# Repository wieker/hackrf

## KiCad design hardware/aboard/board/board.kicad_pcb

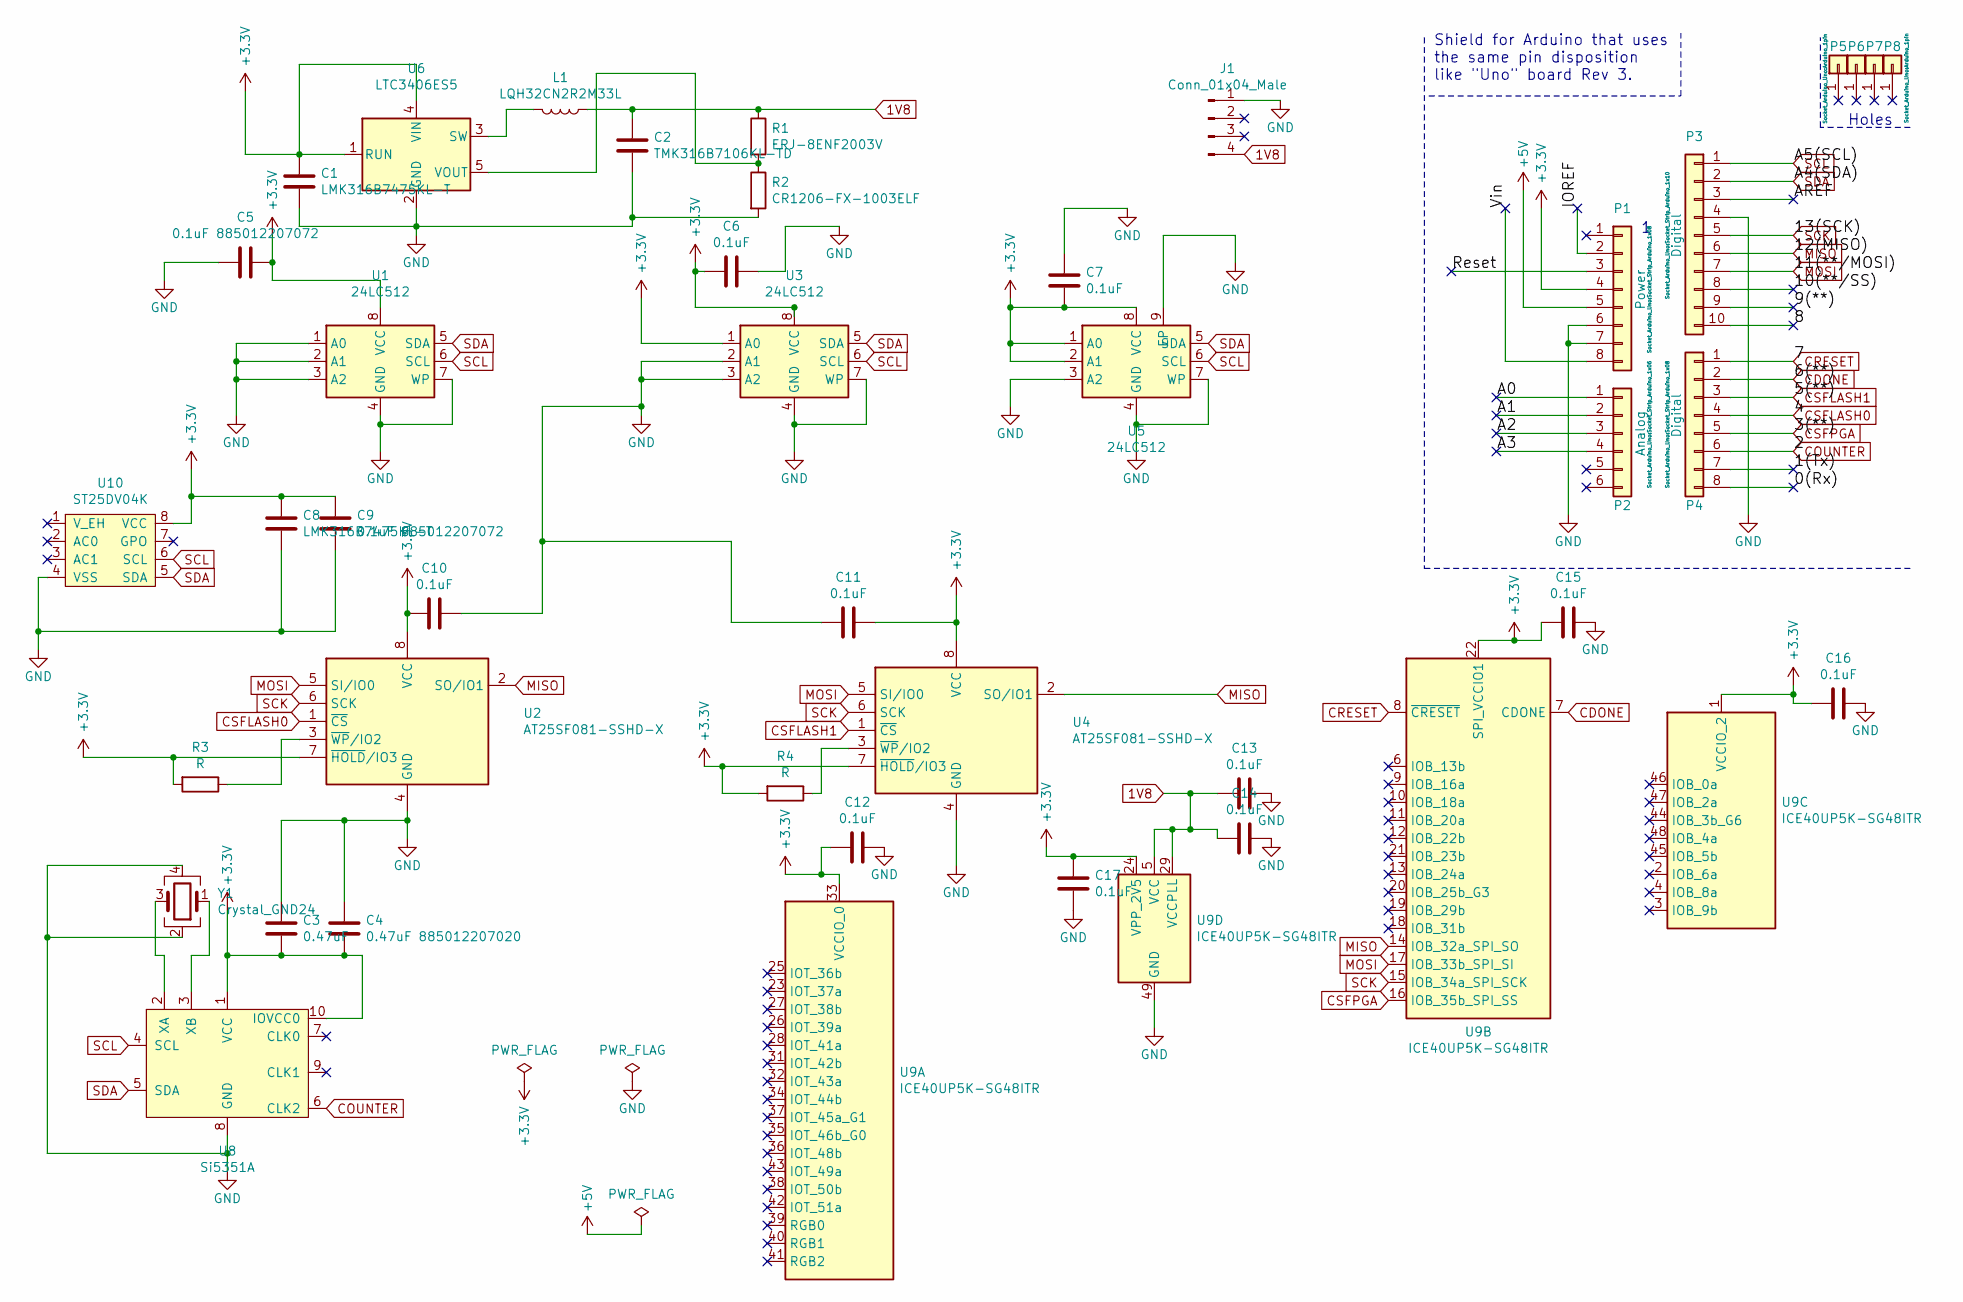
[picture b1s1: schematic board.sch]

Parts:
C1, C8: LMK316B7475KL-T; C_1206_3216Metric
C2: TMK316B7106KL-TD; C_1206_3216Metric
C3: 0.47uF; C_0805_2012Metric
C4: 0.47uF 885012207020; C_0805_2012Metric
C5, C9: 0.1uF 885012207072; C_0805_2012Metric
C6, C7, C10, C11, C12, C13, C14, C15, C16, C17: 0.1uF; C_0805_2012Metric
J1: Conn_01x04_Male; PinHeader_1x04_P2.54mm_Vertical
L1: LQH32CN2R2M33L; L_1210_3225Metric
P1: Power; Socket_Strip_Arduino_1x08
P2: Analog; Socket_Strip_Arduino_1x06
P3: Digital; Socket_Strip_Arduino_1x10
P4: Digital; Socket_Strip_Arduino_1x08
P5, P6, P7, P8: CONN_01X01; Arduino_1pin
R1: ERJ-8ENF2003V; R_1206_3216Metric
R2: CR1206-FX-1003ELF; R_1206_3216Metric
R3, R4: R; R_1206_3216Metric
U1: 24LC512; TSSOP-8_4.4x3mm_P0.65mm
U2, U4: AT25SF081-SSHD-X; SOIC-8_3.9x4.9mm_P1.27mm
U3: 24LC512; SOIC-8_3.9x4.9mm_P1.27mm
U5: 24LC512; DFN-8-1EP_6x5mm_P1.27mm_EP4x4mm
U6: LTC3406ES5; TSOT-23-5
U8: Si5351A; MSOP-10_3x3mm_P0.5mm
U9: ICE40UP5K-SG48ITR; QFN-48-1EP_7x7mm_P0.5mm_EP5.6x5.6mm
U10: ST25DV04K; TSSOP-8_4.4x3mm_P0.65mm
Y1: Crystal_GND24; Crystal_SMD_5032-4Pin_5.0x3.2mm

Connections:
1V8: C2.1, C13.2, C14.2, J1.4, L1.1, R1.1, U9.5 (VCC), U9.29 (VCCPLL), U9.30 (VCC)
+3V3: C1.1, C3.2, C4.2, C5.1, C6.2, C7.1, C8.1, C9.2, C10.2, C11.1, C12.2, C15.2, C16.2, C17.2, P1.4, R3.2, R4.2, U1.8 (VCC), U2.7 (~HOLD~/IO3), U2.8 (VCC), U3.1 (A0), U3.8 (VCC), U4.7 (~HOLD~/IO3), U4.8 (VCC), U5.1 (A0), U5.2 (A1), U5.8 (VCC), U6.1 (RUN), U6.4 (VIN), U8.1 (VCC), U8.10 (IOVCC0), U9.1 (VCCIO_2), U9.22 (SPI_VCCIO1), U9.24 (VPP_2V5), U9.33 (VCCIO_0), U10.8 (VCC)
+5V: P1.5
/0(Rx): P4.8
/1(Tx): P4.7
/8: P3.10
/9(**): P3.9
/10(**/SS): P3.8
/A0: P2.1
/A1: P2.2
/A2: P2.3
/A3: P2.4
/AREF: P3.3
/IOREF: P1.2
/Reset: P1.3
/Vin: P1.8
CDONE: P4.2, U9.7 (CDONE)
COUNTER: P4.6, U8.6 (CLK2)
CRESET: P4.1, U9.8 (~CRESET)
CSFLASH0: P4.4, U2.1 (~CS)
CSFLASH1: P4.3, U4.1 (~CS)
CSFPGA: P4.5, U9.16 (IOB_35b_SPI_SS)
GND: C1.2, C2.2, C3.1, C4.1, C5.2, C6.1, C7.2, C8.2, C9.1, C10.1, C11.2, C12.1, C13.1, C14.1, C15.1, C16.1, C17.1, J1.1, P1.6, P1.7, P3.4, R2.2, U1.1 (A0), U1.2 (A1), U1.3 (A2), U1.4 (GND), U1.7 (WP), U2.4 (GND), U3.2 (A1), U3.3 (A2), U3.4 (GND), U3.7 (WP), U4.4 (GND), U5.3 (A2), U5.4 (GND), U5.7 (WP), U5.9 (EP), U6.2 (GND), U8.8 (GND), U9.49 (GND), U10.4 (VSS), Y1.2, Y1.4
MISO: P3.6, U2.2 (SO/IO1), U4.2 (SO/IO1), U9.14 (IOB_32a_SPI_SO)
MOSI: P3.7, U2.5 (SI/IO0), U4.5 (SI/IO0), U9.17 (IOB_33b_SPI_SI)
unnamed: L1.2, U6.3 (SW)
unnamed: R1.2, R2.1, U6.5 (VOUT)
unnamed: R3.1, U2.3 (~WP~/IO2)
unnamed: R4.1, U4.3 (~WP~/IO2)
unnamed: U8.2 (XA), Y1.3
unnamed: U8.3 (XB), Y1.1
SCK: P3.5, U2.6 (SCK), U4.6 (SCK), U9.15 (IOB_34a_SPI_SCK)
SCL: P3.1, U1.6 (SCL), U3.6 (SCL), U5.6 (SCL), U8.4 (SCL), U10.6 (SCL)
SDA: P3.2, U1.5 (SDA), U3.5 (SDA), U5.5 (SDA), U8.5 (SDA), U10.5 (SDA)

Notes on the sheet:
Holes
Shield for Arduino that uses the same pin disposition like "Uno" board Rev 3.

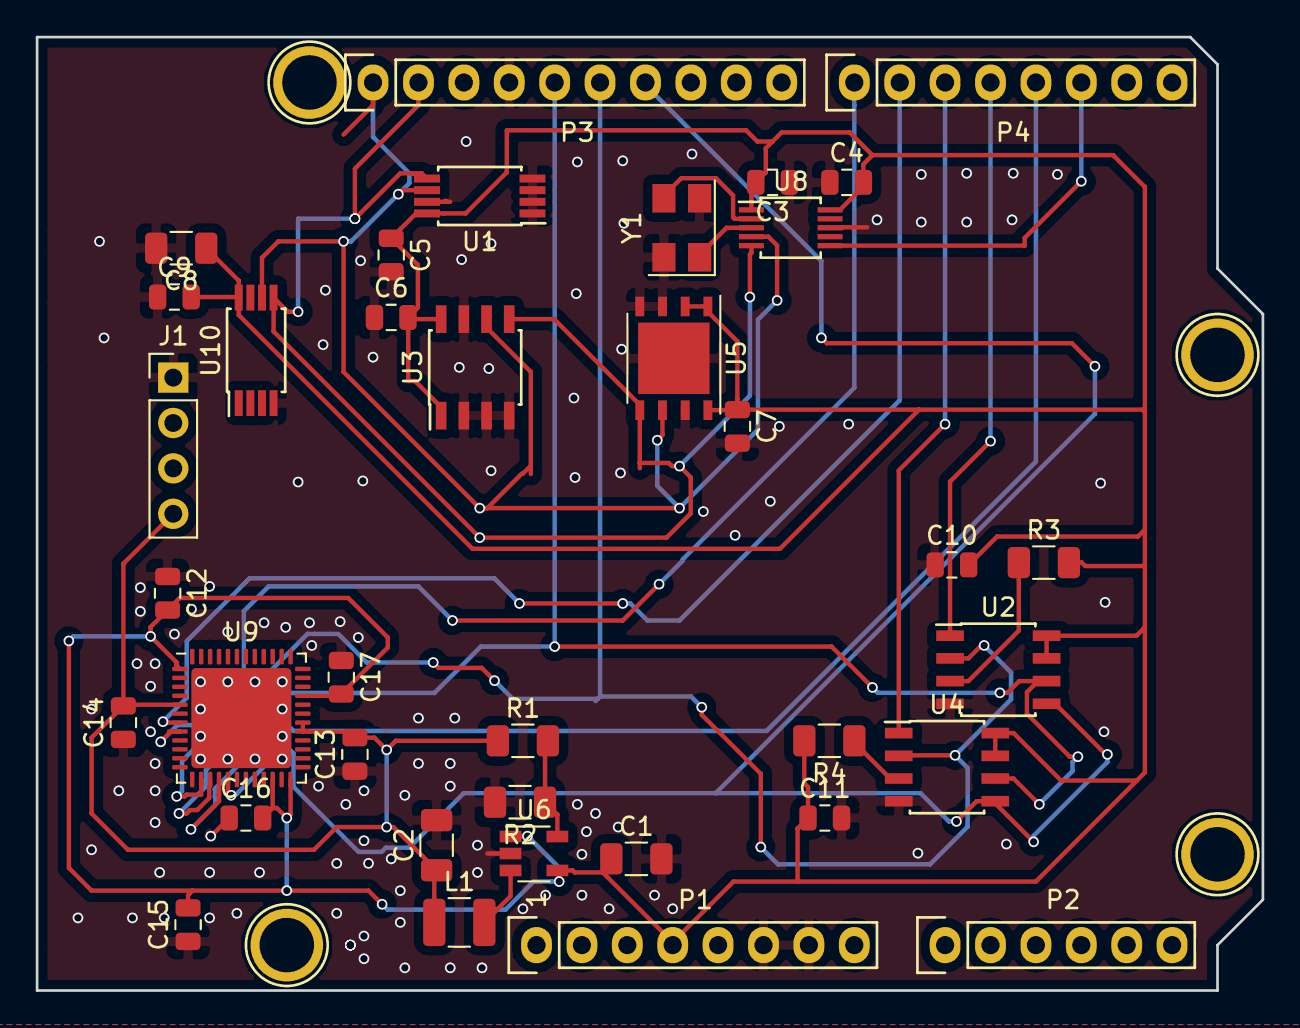
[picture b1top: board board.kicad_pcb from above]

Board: 2 copper layers, 68.6 x 53.3 mm, 41 parts (0 on the bottom side), 20 nets.

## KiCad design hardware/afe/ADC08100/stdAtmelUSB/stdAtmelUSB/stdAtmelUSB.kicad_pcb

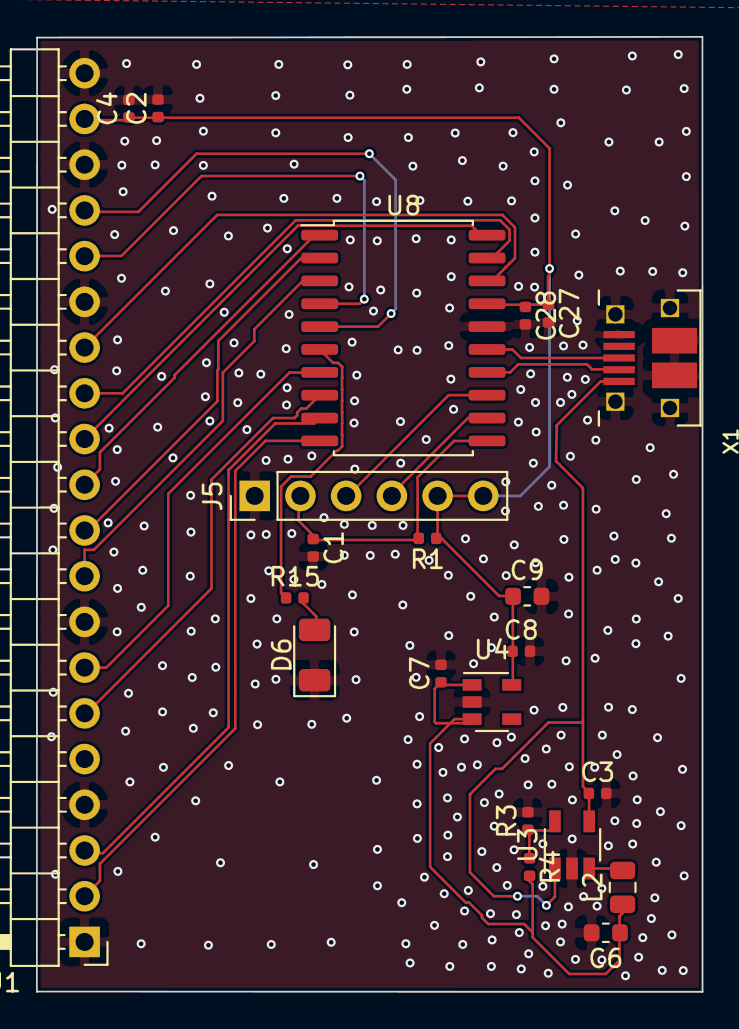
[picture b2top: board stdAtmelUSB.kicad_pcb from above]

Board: 2 copper layers, 37.0 x 53.0 mm, 22 parts (0 on the bottom side), 25 nets.

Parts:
C1, C4, C7, C8, C28: 0.1uF; C_0402_1005Metric
C2, C3, C27: 4.7uF; C_0402_1005Metric
C6, C9: 10uF; C_0603_1608Metric
D6: LED; LED_1206_3216Metric
J1: Conn_01x20_Female; PinHeader_1x20_P2.54mm_Horizontal
J5: Conn_01x06_Male; PinHeader_1x06_P2.54mm_Vertical
L2: 2.2uH; L_0805_2012Metric
R1, R15: 10kOhm; R_0402_1005Metric
R3: 100kOhm; R_0402_1005Metric
R4: 450kOhm; R_0402_1005Metric
U3: LTC3406ES5; TSOT-23-5
U4: MAX40200AUK; SOT-23-5
U8: ATSAMD11D14A-SS; SOIC-20W_7.5x12.8mm_P1.27mm
X1: USBFCI_10103594_MILL; FCI_10103594_MILL

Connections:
+3V3: C2.1, C4.1, C8.1, C9.1, C27.1, C28.1, J1.19, J5.5, J5.6, R1.1, U4.5, U8.17
+5V: C3.1, U3.1, U3.4, X1.VBUS
GND: C1.2, C2.2, C3.2, C4.2, C6.2, C7.2, C8.2, C9.2, C27.2, C28.2, D6.1, J1.1, J1.4, J1.8, J1.15, J1.18, J1.20, J5.1, R3.2, U3.2, U4.2, U8.16, X1.BASE@1, X1.BASE@2, X1.GND, X1.SPRT@1, X1.SPRT@2, X1.SPRT@3, X1.SPRT@4
unnamed: C6.1, C7.1, L2.1, R4.2, U4.1, U4.3
unnamed: D6.2, R15.2
unnamed: L2.2, U3.3
unnamed: R3.1, R4.1, U3.5
unnamed: U8.14, X1.D-
unnamed: U8.15, X1.D+
fpga_cdone: J1.14, U8.18
fpga_reset: J1.13, U8.19
led_mcu: R15.1, U8.6
nrf_rx: J1.3, U8.9
nrf_tx: J1.2, U8.10
spi_clk: J1.12, U8.20
spi_miso: J1.10, U8.2
spi_mosi: J1.9, U8.3
spi_ss: J1.11, U8.1
swd_clk: J5.4, U8.12
swd_io: J5.3, U8.13
swd_rst: C1.1, J5.2, R1.2, U8.11
uart_fpga_rx_2: J1.6, U8.8
uart_fpga_tx_2: J1.7, U8.7
uart_rx: J1.17, U8.5
uart_tx: J1.16, U8.4

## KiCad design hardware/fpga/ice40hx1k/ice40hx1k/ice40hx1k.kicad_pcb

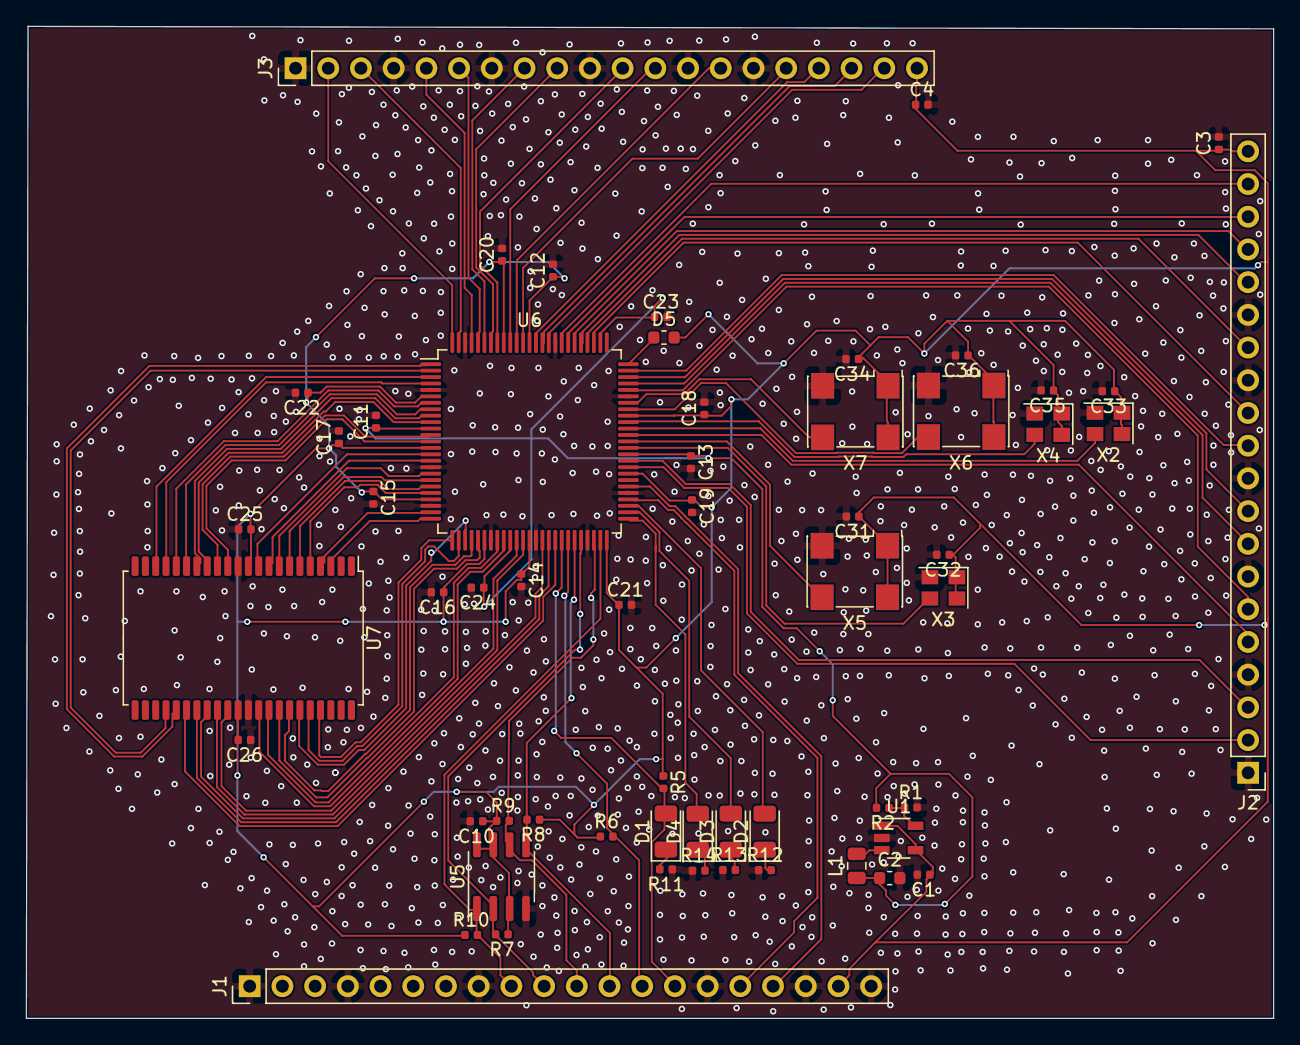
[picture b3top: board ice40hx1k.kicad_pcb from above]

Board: 2 copper layers, 96.8 x 77.0 mm, 58 parts (0 on the bottom side), 83 nets.

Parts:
C1: 4.7uF; C_0402_1005Metric
C2: 10uF; C_0603_1608Metric
C3, C4: 1uF; C_0402_1005Metric
C10, C11, C12, C13, C14, C15, C16, C17, C18, C19, C20, C21, C22, C23, C24, C25, C26: 0.1uF; C_0402_1005Metric
C31, C32, C33, C34, C35, C36: 0.01uF; C_0402_1005Metric
D1, D2, D3, D4: LED; LED_1206_3216Metric
D5: CDBU05; C_0603_1608Metric
J1, J2, J3: Conn_01x20_Male; PinHeader_1x20_P2.54mm_Vertical
L1: 2.2uH; L_0805_2012Metric
R1, R2: 100kOhm; R_0402_1005Metric
R5, R6, R7, R8, R9, R10: 10kOhm; R_0402_1005Metric
R11, R12, R13, R14: 10kohm; R_0402_1005Metric
U1: LTC3406ES5; TSOT-23-5
U5: AT25SF081-SSHD-X; SOIC-8_3.9x4.9mm_P1.27mm
U6: ICE40HX1K-VQ100(VQFP100); LQFP-100_14x14mm_P0.5mm
U7: AS7C34096A; TSOP-II-44_10.16x18.41mm_P0.8mm
X2, X3, X4: ASE-10MHz; Oscillator_SMD_Abracon_ASE-4Pin_3.2x2.5mm
X5, X6, X7: ASV-xxxMHz; Oscillator_SMD_Abracon_ASV-4Pin_7.0x5.1mm

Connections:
+1V2: C2.1, C11.1, C13.1, C23.1, C24.1, L1.1, R2.2, U6.11, U6.35, U6.61, U6.77
+3V3: C1.1, C3.1, C4.1, C10.1, C12.1, C14.1, C15.1, C16.1, C17.1, C18.1, C19.1, C20.1, C21.1, C22.1, C25.2, C26.2, C31.1, C32.1, C33.1, C34.1, C35.1, C36.1, D5.2, J1.19, J2.20, J3.20, R5.1, R6.1, R7.1, R8.1, R9.1, R10.1, U1.1, U1.4, U5.3, U5.7, U5.8, U6.6, U6.14, U6.22, U6.31, U6.38, U6.50, U6.58, U6.67, U6.88, U6.92, U7.11, U7.33, X2.1, X2.4, X3.1, X3.4, X4.1, X4.4, X5.1, X5.4, X6.1, X6.4, X7.1, X7.4
CDONE: D1.2, J1.14, R5.2, U6.43
CRESET: J1.13, R6.2, U6.44
GND: C1.2, C2.2, C3.2, C4.2, C10.2, C11.2, C12.2, C13.2, C14.2, C15.2, C16.2, C17.2, C18.2, C19.2, C20.2, C21.2, C22.2, C23.2, C24.2, C25.1, C26.1, C31.2, C32.2, C33.2, C34.2, C35.2, C36.2, J1.1, J1.4, J1.8, J1.15, J1.18, J1.20, J2.1, J2.4, J2.7, J2.10, J2.13, J2.15, J3.1, J3.4, J3.7, J3.10, J3.13, J3.15, R1.2, R11.1, R12.1, R13.1, R14.1, U1.2, U5.4, U6.5, U6.17, U6.23, U6.32, U6.39, U6.47, U6.55, U6.70, U6.84, U6.98, U7.12, U7.34, X2.2, X3.2, X4.2, X5.2, X6.2, X7.2
IO1: U6.1, U7.27
IO2: U6.2, U7.26
IO3: U6.3, U7.20
IO4: U6.4, U7.19
IO7: U6.7, U7.18
IO8: U6.8, U7.17
IO9: U6.9, U7.16
IO10: U6.10, U7.15
IO12: U6.12, U7.14
IO13: U6.13, U7.13
IO15: U6.15, U7.10
IO16: U6.16, U7.9
IO18: U6.18, U7.8
IO19: U6.19, U7.7
IO20: U6.20, U7.6
IO21: U6.21, U7.5
IO24: U6.24, U7.4
IO25: U6.25, U7.3
IO26: U6.26, U7.41
IO27: U6.27, U7.40
IO28: U6.28, U7.39
IO29: U6.29, U7.38
IO30: U6.30, U7.37
IO33: U6.33, U7.36
IO34: U6.34, U7.35
IO36: U6.36, U7.32
IO37: U6.37, U7.31
IO40: U6.40, U7.30
IO41: U6.41, U7.29
IO43: U6.42, U7.28
IO51: D4.2, U6.51
IO52: D3.2, U6.52
IO53: D2.2, U6.53
IO54: J1.16, U6.54
IO56: J1.17, U6.56
IO59: J2.2, U6.59
IO60: J2.3, U6.60
IO62: U6.62, X3.3
IO63: U6.63, X5.3
IO64: J2.5, U6.64
IO65: U6.65, X2.3
IO66: U6.66, X4.3
IO68: U6.68, X6.3
IO69: U6.69, X7.3
IO71: J2.6, U6.71
IO72: J2.8, U6.72
IO73: J2.9, U6.73
IO74: J2.11, U6.74
IO78: J2.12, U6.78
IO79: J2.14, U6.79
IO80: J2.16, U6.80
IO81: J2.17, U6.81
IO82: J2.18, U6.82
IO83: J2.19, U6.83
IO85: J3.19, U6.85
IO86: J3.18, U6.86
IO87: J3.17, U6.87
IO89: J3.16, U6.89
IO90: J3.14, U6.90
IO91: J3.12, U6.91
IO93: J3.11, U6.93
IO94: J3.9, U6.94
IO95: J3.8, U6.95
IO96: J3.6, U6.96
IO97: J3.5, U6.97
IO99: J3.3, U6.99
IO100: J3.2, U6.100
unnamed: D1.1, R11.2
unnamed: D2.1, R12.2
unnamed: D3.1, R13.2
unnamed: D4.1, R14.2
unnamed: D5.1, U6.75
unnamed: L1.2, U1.3
unnamed: R1.1, R2.1, U1.5
SPI_CS: J1.9, R10.2, U5.1, U6.49
SPI_IN: J1.10, R7.2, U5.2, U6.46
SPI_OUT: J1.12, R8.2, U5.5, U6.45
SPI_SCK: J1.11, R9.2, U5.6, U6.48

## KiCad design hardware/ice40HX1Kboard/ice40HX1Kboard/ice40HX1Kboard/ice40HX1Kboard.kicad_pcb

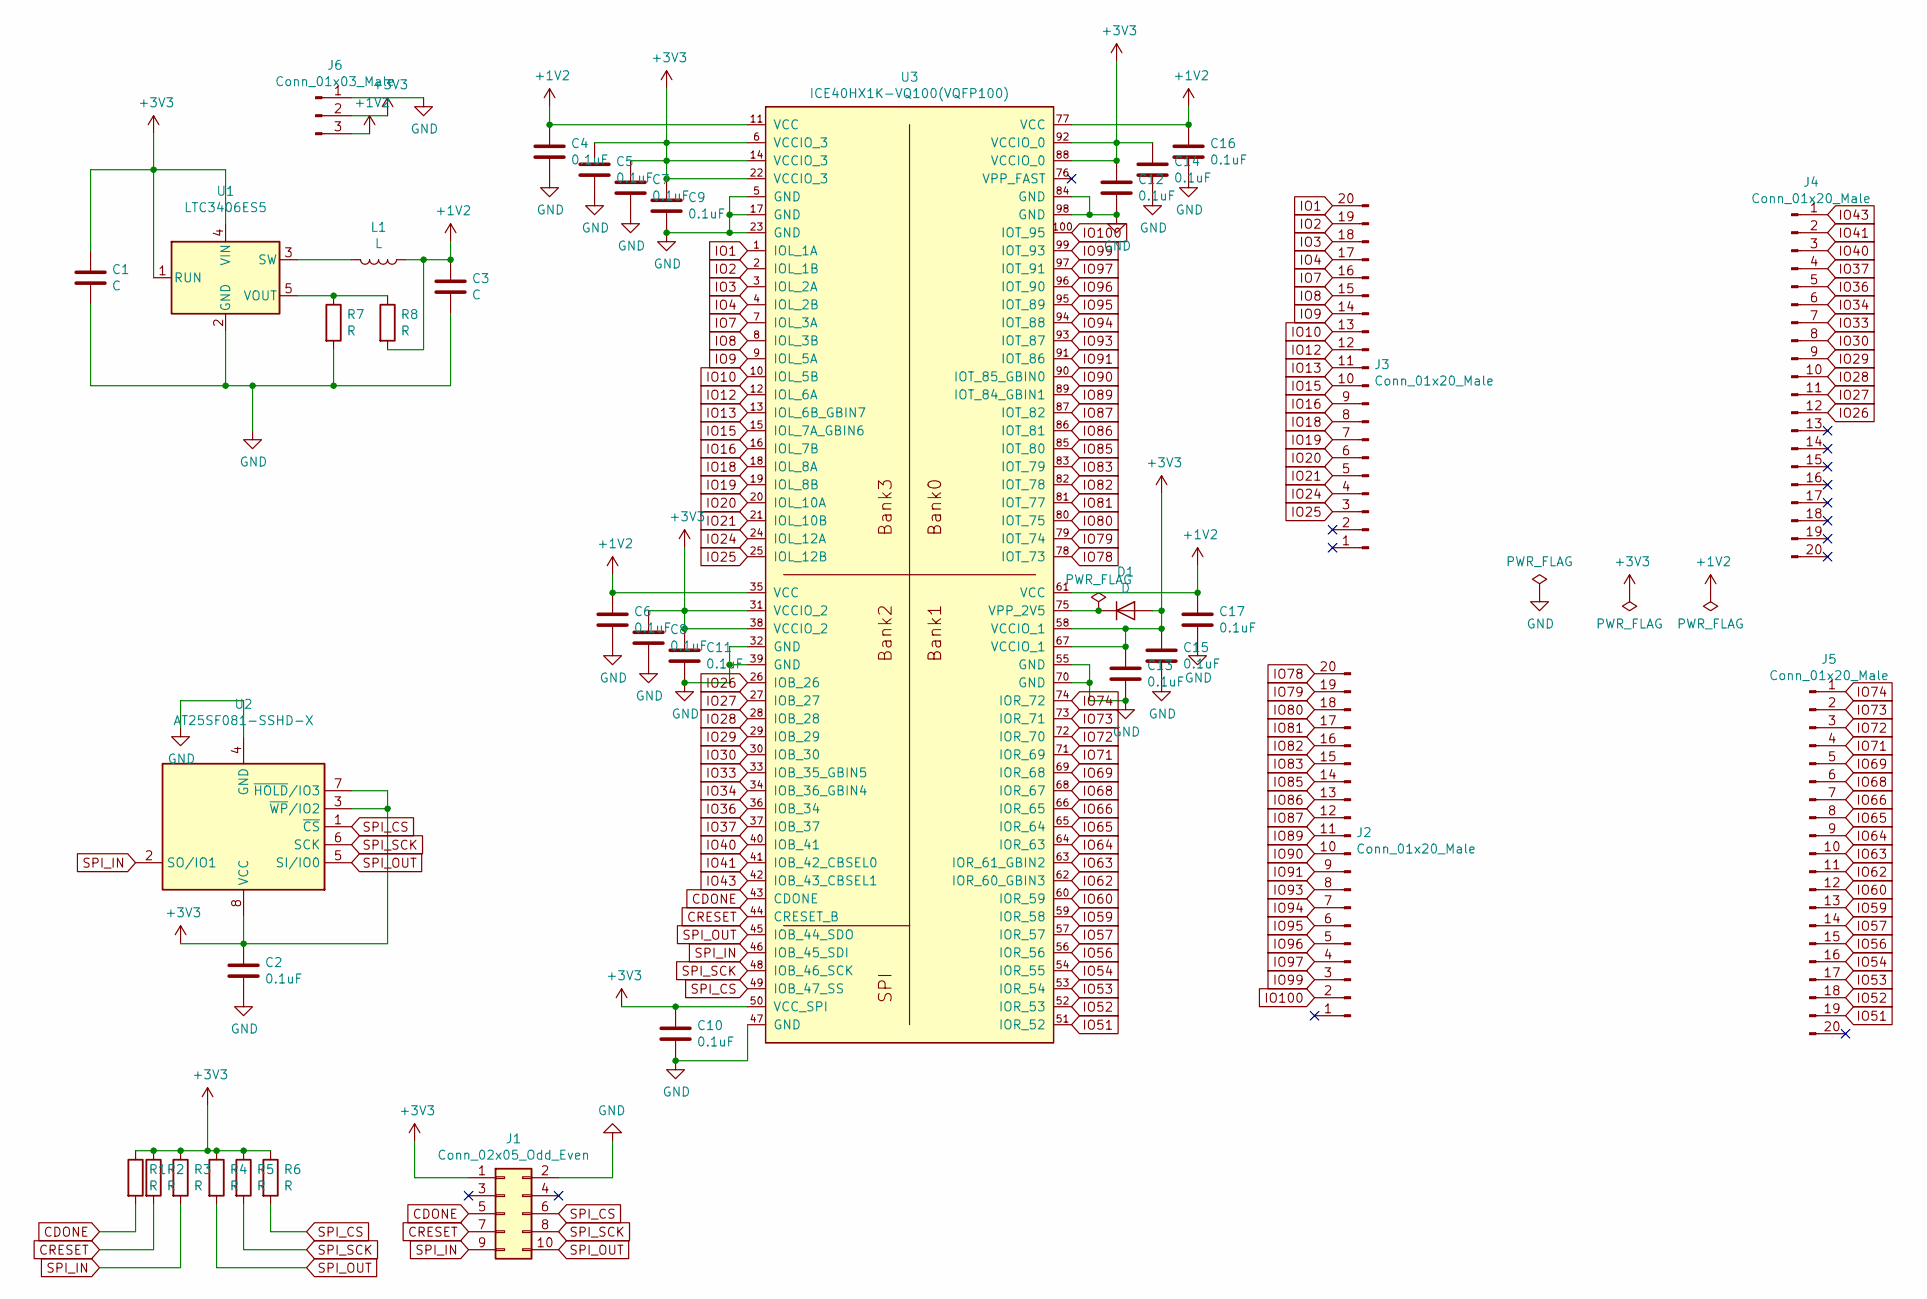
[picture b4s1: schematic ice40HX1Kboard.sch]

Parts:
C1, C3: C; C_1206_3216Metric
C2, C4, C5, C6, C7, C8, C9, C10, C11, C12, C13, C14, C15, C16, C17: 0.1uF; C_0805_2012Metric
D1: D; C_0603_1608Metric
J1: Conn_02x05_Odd_Even; PinHeader_2x05_P2.54mm_Vertical
J2, J3, J4, J5: Conn_01x20_Male; PinHeader_1x20_P2.54mm_Vertical
J6: Conn_01x03_Male; PinHeader_1x03_P2.54mm_Vertical
L1: L; L_1210_3225Metric
R1, R2, R3, R4, R5, R6, R7, R8: R; R_1206_3216Metric
U1: LTC3406ES5; TSOT-23-5
U2: AT25SF081-SSHD-X; SOIC-8_3.9x4.9mm_P1.27mm
U3: ICE40HX1K-VQ100(VQFP100); LQFP-100_14x14mm_P0.5mm

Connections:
+1V2: C3.1, C4.1, C6.1, C16.1, C17.1, J6.3, L1.1, R8.2, U3.11 (VCC), U3.35 (VCC), U3.61 (VCC), U3.77 (VCC)
+3V3: C1.1, C2.1, C5.1, C7.1, C8.1, C9.1, C10.1, C11.1, C12.1, C13.1, C14.1, C15.1, D1.2 (A), J1.1, J6.2, R1.1, R2.1, R3.1, R4.1, R5.1, R6.1, U1.1 (RUN), U1.4 (VIN), U2.3 (~WP~/IO2), U2.7 (~HOLD~/IO3), U2.8 (VCC), U3.6 (VCCIO_3), U3.14 (VCCIO_3), U3.22 (VCCIO_3), U3.31 (VCCIO_2), U3.38 (VCCIO_2), U3.50 (VCC_SPI), U3.58 (VCCIO_1), U3.67 (VCCIO_1), U3.88 (VCCIO_0), U3.92 (VCCIO_0)
CDONE: J1.5, R1.2, U3.43 (CDONE)
CRESET: J1.7, R2.2, U3.44 (CRESET_B)
GND: C1.2, C2.2, C3.2, C4.2, C5.2, C6.2, C7.2, C8.2, C9.2, C10.2, C11.2, C12.2, C13.2, C14.2, C15.2, C16.2, C17.2, J1.2, J6.1, R7.2, U1.2 (GND), U2.4 (GND), U3.5 (GND), U3.17 (GND), U3.23 (GND), U3.32 (GND), U3.39 (GND), U3.47 (GND), U3.55 (GND), U3.70 (GND), U3.84 (GND), U3.98 (GND)
IO1: J3.20, U3.1 (IOL_1A)
IO2: J3.19, U3.2 (IOL_1B)
IO3: J3.18, U3.3 (IOL_2A)
IO4: J3.17, U3.4 (IOL_2B)
IO7: J3.16, U3.7 (IOL_3A)
IO8: J3.15, U3.8 (IOL_3B)
IO9: J3.14, U3.9 (IOL_5A)
IO10: J3.13, U3.10 (IOL_5B)
IO12: J3.12, U3.12 (IOL_6A)
IO13: J3.11, U3.13 (IOL_6B_GBIN7)
IO15: J3.10, U3.15 (IOL_7A_GBIN6)
IO16: J3.9, U3.16 (IOL_7B)
IO18: J3.8, U3.18 (IOL_8A)
IO19: J3.7, U3.19 (IOL_8B)
IO20: J3.6, U3.20 (IOL_10A)
IO21: J3.5, U3.21 (IOL_10B)
IO24: J3.4, U3.24 (IOL_12A)
IO25: J3.3, U3.25 (IOL_12B)
IO26: J4.12, U3.26 (IOB_26)
IO27: J4.11, U3.27 (IOB_27)
IO28: J4.10, U3.28 (IOB_28)
IO29: J4.9, U3.29 (IOB_29)
IO30: J4.8, U3.30 (IOB_30)
IO33: J4.7, U3.33 (IOB_35_GBIN5)
IO34: J4.6, U3.34 (IOB_36_GBIN4)
IO36: J4.5, U3.36 (IOB_34)
IO37: J4.4, U3.37 (IOB_37)
IO40: J4.3, U3.40 (IOB_41)
IO41: J4.2, U3.41 (IOB_42_CBSEL0)
IO43: J4.1, U3.42 (IOB_43_CBSEL1)
IO51: J5.19, U3.51 (IOR_52)
IO52: J5.18, U3.52 (IOR_53)
IO53: J5.17, U3.53 (IOR_54)
IO54: J5.16, U3.54 (IOR_55)
IO56: J5.15, U3.56 (IOR_56)
IO57: J5.14, U3.57 (IOR_57)
IO59: J5.13, U3.59 (IOR_58)
IO60: J5.12, U3.60 (IOR_59)
IO62: J5.11, U3.62 (IOR_60_GBIN3)
IO63: J5.10, U3.63 (IOR_61_GBIN2)
IO64: J5.9, U3.64 (IOR_63)
IO65: J5.8, U3.65 (IOR_64)
IO66: J5.7, U3.66 (IOR_65)
IO68: J5.6, U3.68 (IOR_67)
IO69: J5.5, U3.69 (IOR_68)
IO71: J5.4, U3.71 (IOR_69)
IO72: J5.3, U3.72 (IOR_70)
IO73: J5.2, U3.73 (IOR_71)
IO74: J5.1, U3.74 (IOR_72)
IO78: J2.20, U3.78 (IOT_73)
IO79: J2.19, U3.79 (IOT_74)
IO80: J2.18, U3.80 (IOT_75)
IO81: J2.17, U3.81 (IOT_77)
IO82: J2.16, U3.82 (IOT_78)
IO83: J2.15, U3.83 (IOT_79)
IO85: J2.14, U3.85 (IOT_80)
IO86: J2.13, U3.86 (IOT_81)
IO87: J2.12, U3.87 (IOT_82)
IO89: J2.11, U3.89 (IOT_84_GBIN1)
IO90: J2.10, U3.90 (IOT_85_GBIN0)
IO91: J2.9, U3.91 (IOT_86)
IO93: J2.8, U3.93 (IOT_87)
IO94: J2.7, U3.94 (IOT_88)
IO95: J2.6, U3.95 (IOT_89)
IO96: J2.5, U3.96 (IOT_90)
IO97: J2.4, U3.97 (IOT_91)
IO99: J2.3, U3.99 (IOT_93)
IO100: J2.2, U3.100 (IOT_95)
unnamed: D1.1 (K), U3.75 (VPP_2V5)
unnamed: L1.2, U1.3 (SW)
unnamed: R7.1, R8.1, U1.5 (VOUT)
SPI_CS: J1.6, R6.2, U2.1 (~CS), U3.49 (IOB_47_SS)
SPI_IN: J1.9, R3.2, U2.2 (SO/IO1), U3.46 (IOB_45_SDI)
SPI_OUT: J1.10, R4.2, U2.5 (SI/IO0), U3.45 (IOB_44_SDO)
SPI_SCK: J1.8, R5.2, U2.6 (SCK), U3.48 (IOB_46_SCK)

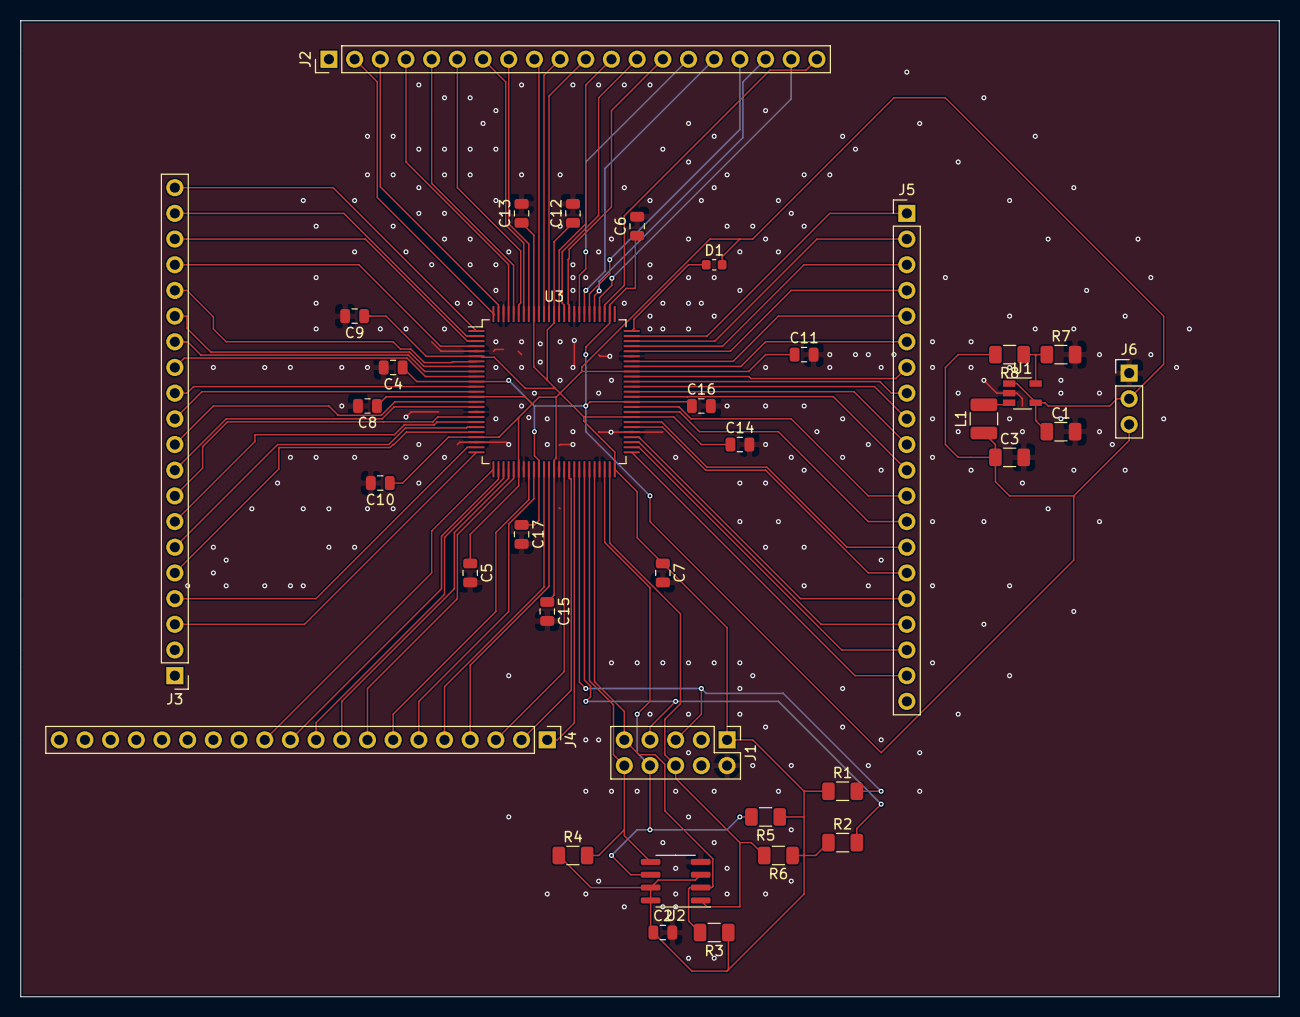
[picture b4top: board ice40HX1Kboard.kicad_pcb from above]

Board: 2 copper layers, 124.5 x 96.5 mm, 36 parts (0 on the bottom side), 80 nets.

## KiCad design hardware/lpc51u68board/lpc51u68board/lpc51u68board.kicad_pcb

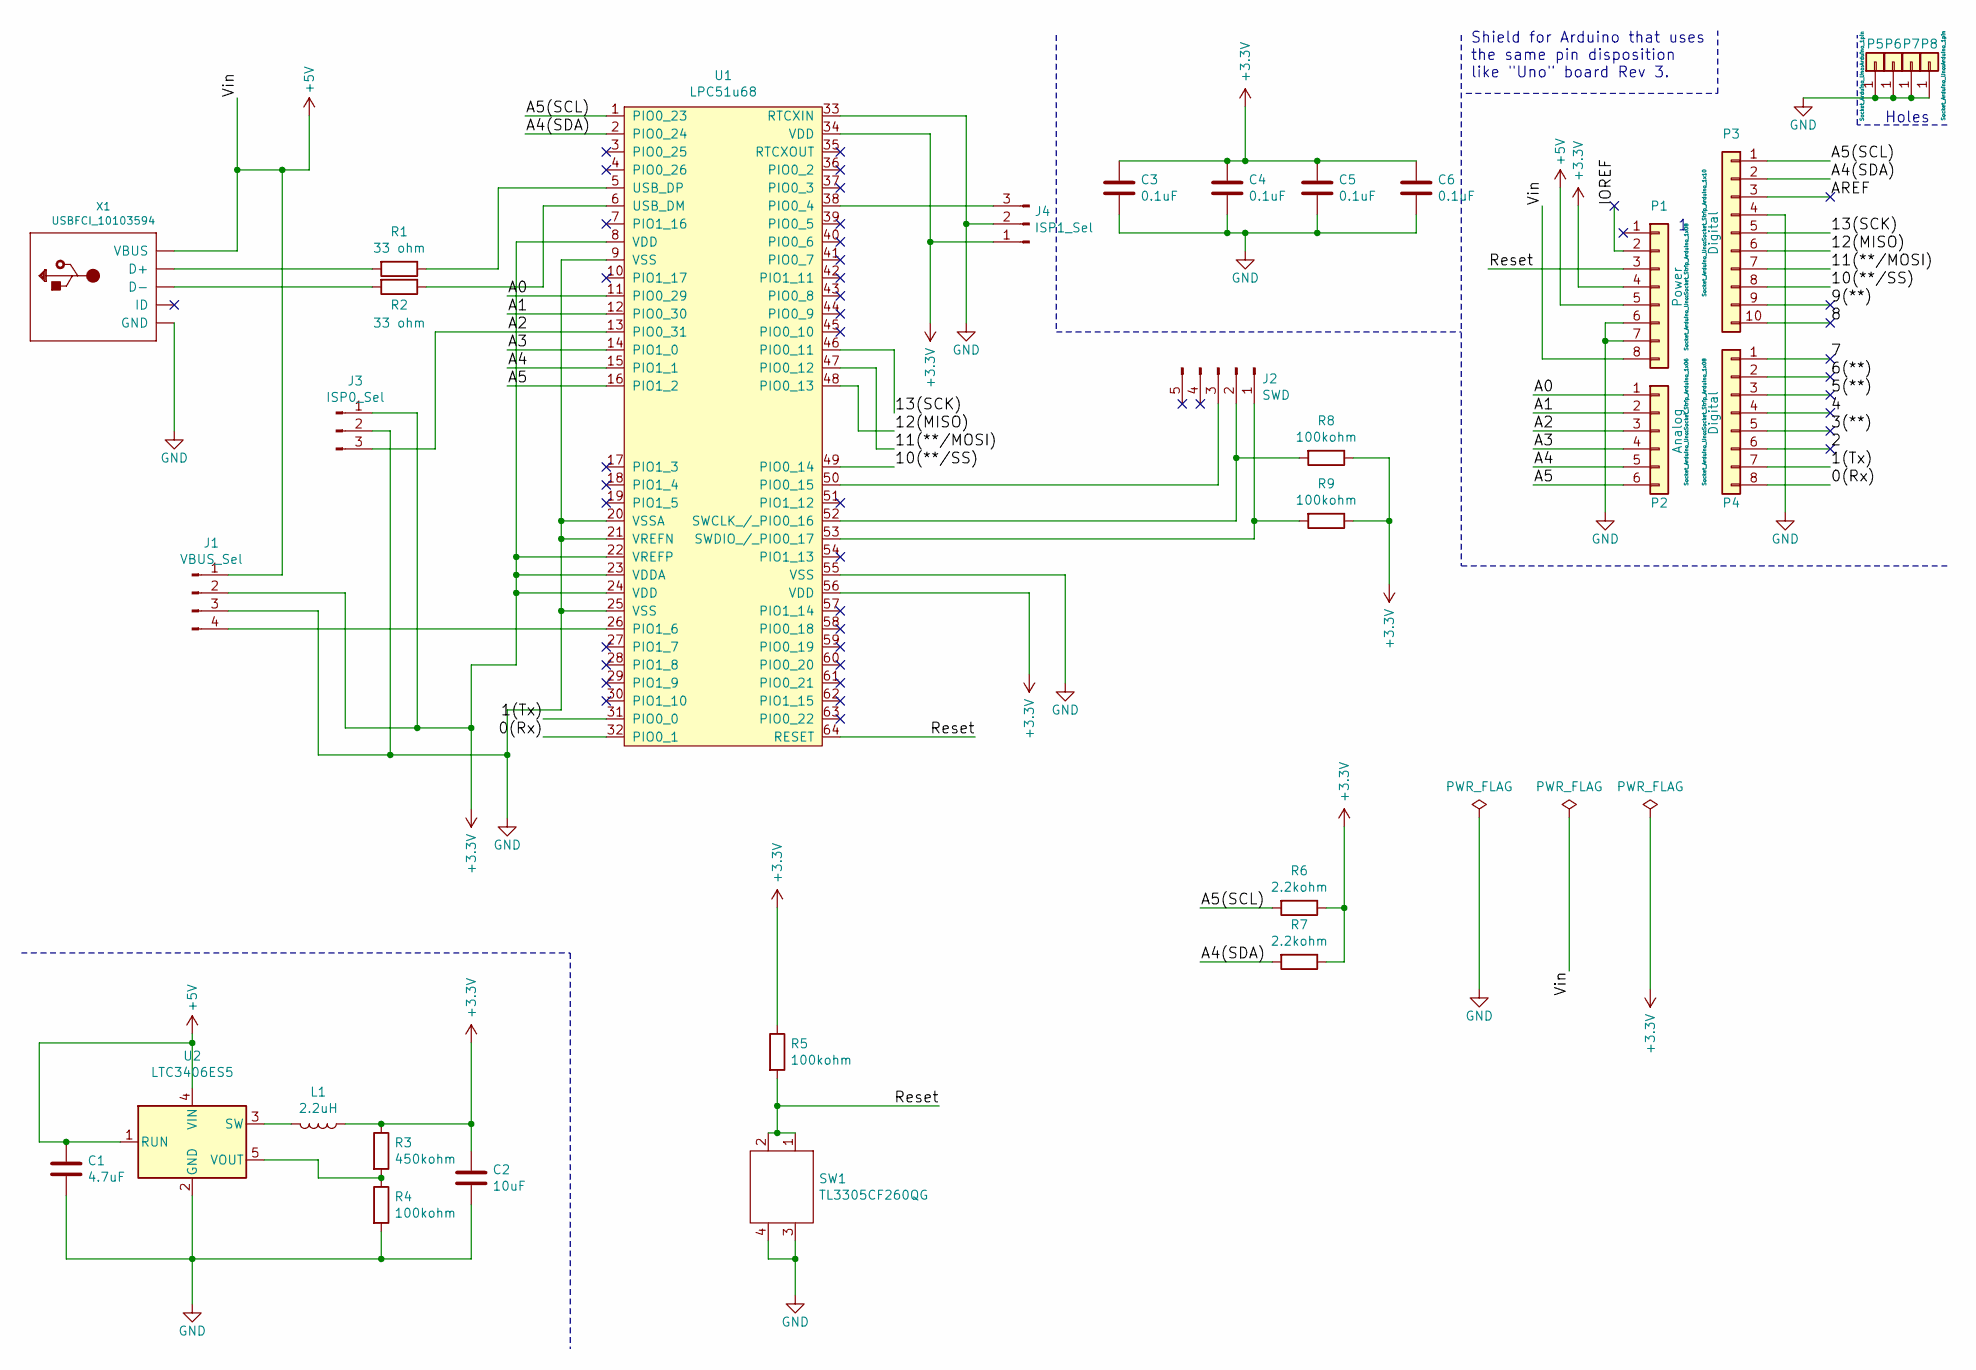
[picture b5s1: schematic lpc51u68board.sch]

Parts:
C1: 4.7uF; C_1206_3216Metric
C2: 10uF; C_1206_3216Metric
C3, C4, C5, C6: 0.1uF; C_0805_2012Metric
J1: VBUS_Sel; PinHeader_1x04_P2.54mm_Vertical
J2: SWD; PinHeader_1x05_P2.54mm_Vertical
J3: ISP0_Sel; PinHeader_1x03_P2.54mm_Vertical
J4: ISP1_Sel; PinHeader_1x03_P2.54mm_Vertical
L1: 2.2uH; L_1210_3225Metric
P1: Power; Socket_Strip_Arduino_1x08
P2: Analog; Socket_Strip_Arduino_1x06
P3: Digital; Socket_Strip_Arduino_1x10
P4: Digital; Socket_Strip_Arduino_1x08
P5, P6, P7, P8: CONN_01X01; Arduino_1pin
R1, R2: 33 ohm; R_0805_2012Metric
R3: 450kohm; R_1206_3216Metric
R4, R5, R8, R9: 100kohm; R_1206_3216Metric
R6, R7: 2.2kohm; R_0805_2012Metric
SW1: TL3305CF260QG; TL3305-C
U1: LPC51u68; LQFP-64_10x10mm_P0.5mm
U2: LTC3406ES5; TSOT-23-5
X1: USBFCI_10103594; FCI_10103594_MILL

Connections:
+3V3: C2.1, C3.1, C4.1, C5.1, C6.1, J1.2, J3.1, J4.1, L1.1, P1.4, R3.1, R5.1, R6.1, R7.1, R8.1, R9.1, U1.8 (VDD), U1.22 (VREFP), U1.23 (VDDA), U1.24 (VDD), U1.34 (VDD), U1.56 (VDD)
+5V: C1.1, J1.1, P1.5, P1.8, U2.1 (RUN), U2.4 (VIN), X1.VBUS
/0(Rx): P4.8, U1.32 (PIO0_1)
/1(Tx): P4.7, U1.31 (PIO0_0)
/2: P4.6
/3(**): P4.5
/4: P4.4
/5(**): P4.3
/6(**): P4.2
/7: P4.1
/8: P3.10
/9(**): P3.9
/10(**/SS): P3.8, U1.49 (PIO0_14)
/11(**/MOSI): P3.7, U1.47 (PIO0_12)
/12(MISO): P3.6, U1.48 (PIO0_13)
/13(SCK): P3.5, U1.46 (PIO0_11)
/A0: P2.1, U1.11 (PIO0_29)
/A1: P2.2, U1.12 (PIO0_30)
/A2: J3.3, P2.3, U1.13 (PIO0_31)
/A3: P2.4, U1.14 (PIO1_0)
/A4: P2.5, U1.15 (PIO1_1)
/A4(SDA): P3.2, R7.2, U1.2 (PIO0_24)
/A5: P2.6, U1.16 (PIO1_2)
/A5(SCL): P3.1, R6.2, U1.1 (PIO0_23)
/AREF: P3.3
/IOREF: P1.2
/Reset: P1.3, R5.2, SW1.1, SW1.2, U1.64 (RESET)
GND: C1.2, C2.2, C3.2, C4.2, C5.2, C6.2, J1.3, J3.2, J4.2, P1.6, P1.7, P3.4, P5.1, P6.1, P7.1, P8.1, R4.2, SW1.3, SW1.4, U1.9 (VSS), U1.20 (VSSA), U1.21 (VREFN), U1.25 (VSS), U1.33 (RTCXIN), U1.55 (VSS), U2.2 (GND), X1.BASE@1 (GND), X1.BASE@2 (GND), X1.GND, X1.SPRT@1 (GND), X1.SPRT@2 (GND), X1.SPRT@3 (GND), X1.SPRT@4 (GND)
unnamed: J1.4, U1.26 (PIO1_6)
unnamed: J2.1, R9.2, U1.53 (SWDIO_/_PIO0_17)
unnamed: J2.2, R8.2, U1.52 (SWCLK_/_PIO0_16)
unnamed: J2.3, U1.50 (PIO0_15)
unnamed: J4.3, U1.38 (PIO0_4)
unnamed: L1.2, U2.3 (SW)
unnamed: R1.1, U1.5 (USB_DP)
unnamed: R1.2, X1.D+
unnamed: R2.1, U1.6 (USB_DM)
unnamed: R2.2, X1.D-
unnamed: R3.2, R4.1, U2.5 (VOUT)

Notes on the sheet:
Holes
Shield for Arduino that uses the same pin disposition like "Uno" board Rev 3.

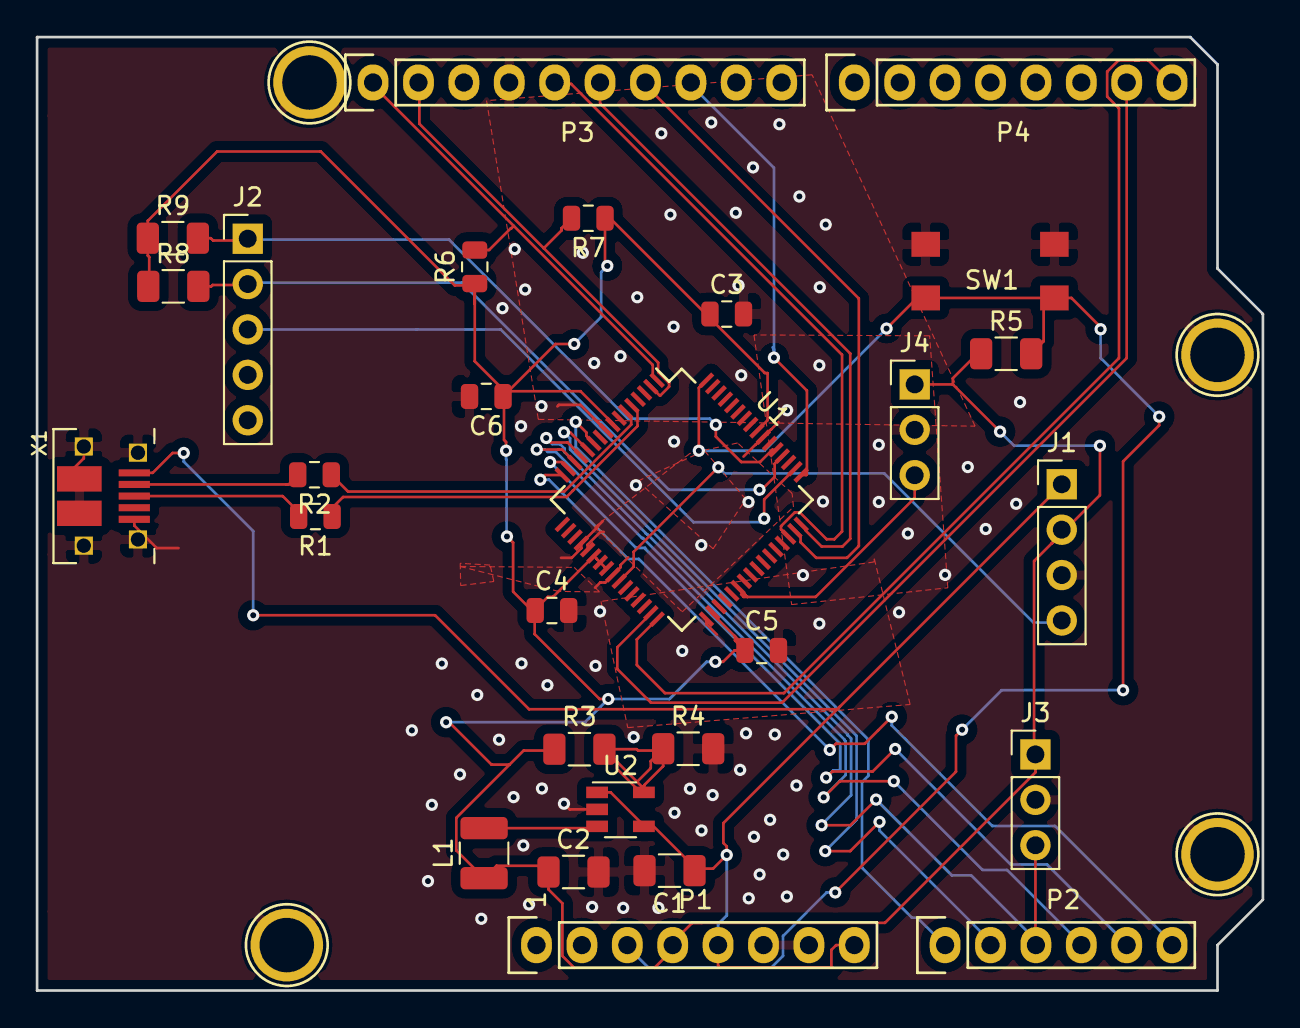
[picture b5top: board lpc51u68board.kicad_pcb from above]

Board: 2 copper layers, 68.6 x 53.3 mm, 32 parts (0 on the bottom side), 29 nets.
